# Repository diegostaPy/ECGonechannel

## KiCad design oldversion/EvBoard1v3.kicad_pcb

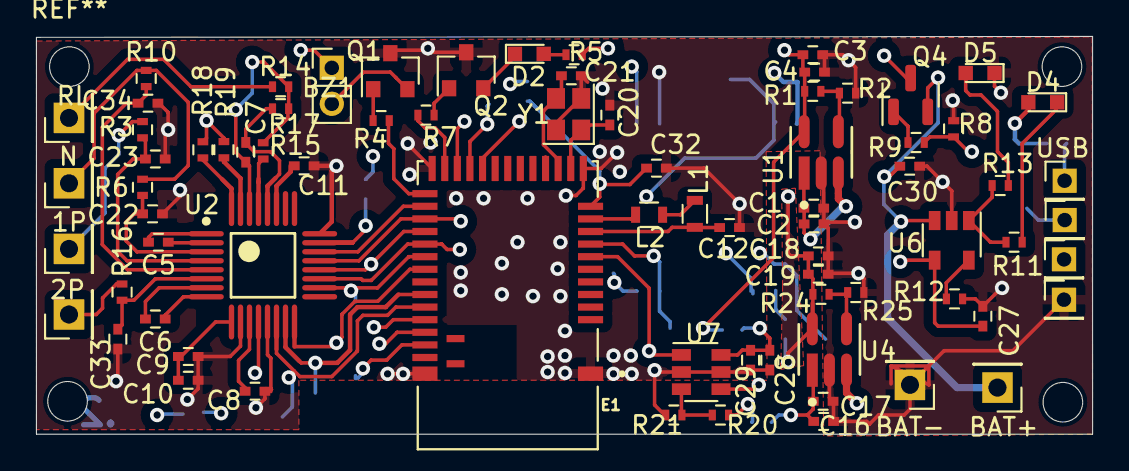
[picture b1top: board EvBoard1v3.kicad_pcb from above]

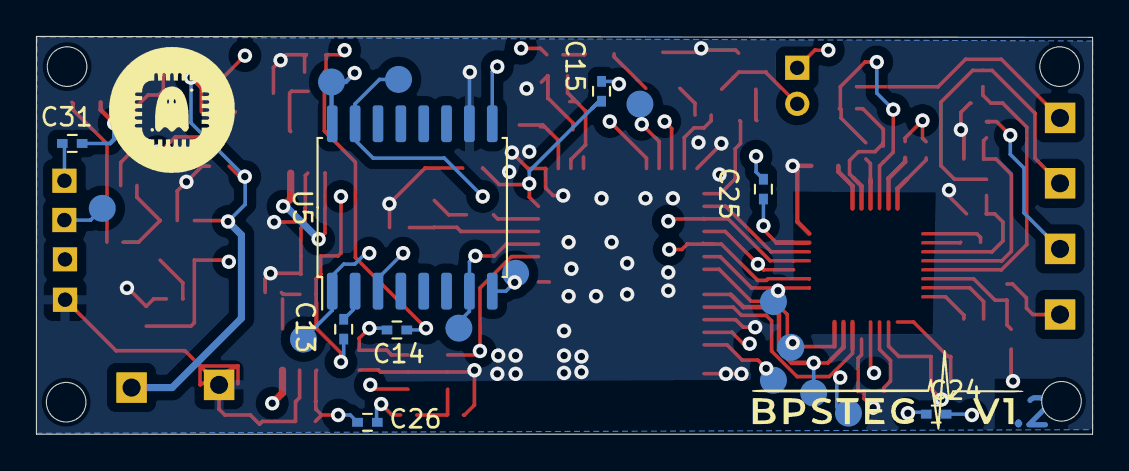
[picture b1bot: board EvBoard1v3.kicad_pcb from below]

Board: 4 copper layers, 58.7 x 22.1 mm, 91 parts (15 on the bottom side), 68 nets.

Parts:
1P, 2P: In_sensor1N; Pin_Header_Straight_1x01_Pitch2.54mm
BAT+: Conn_01x01; Pin_Header_Straight_1x01_Pitch2.54mm
BAT-: conn_gnd1; Pin_Header_Straight_1x01_Pitch2.54mm
BZ1: Buzzer; Pin_Header_Straight_1x02_Pitch2.00mm
C1, C3, C8, C11, C12, C16, C18, C27, C28, C30: 1uF; C_0402
C2, C4, C9, C17, C19, C29: 0.1uF; C_0402
C5, C6: 4.7nF; C_0402
C7: 1.5nF; C_0402
C10, C32: 10uF; C_0402
C13, C14, C15, C24, C25, C26, C31: 0; C_0402
C20, C21: 12pF; C_0402
C22, C23, C33, C34: 47pF; C_0402
D2, D4, D5: LED_Small; LED_0603
E1: MDBT42Q-512KV2; RAYTAC_MDBT42Q-512KV2
J6, J7, J8: Conn_01x01_Female; Pin_Header_Straight_1x01_Pitch2.00mm
L1: 10uH; L_0603
L2: 15nH; L_0603
N: In_sensor1; Pin_Header_Straight_1x01_Pitch2.54mm
Q1, Q2: Q_NPN_BCE; SOT-23
Q4: Q_PMOS_GSD; SOT-23
R1, R24: R1; R_0402
R2, R25: R2; R_0402
R3, R6, R10, R16, R18, R19: 30k; R_0402
R4, R7, R12: 2.2k; R_0402
R5, R11, R13: 470; R_0402
R8, R9, R20: 1k; R_0402
R14, R15: 100k; R_0402
R17: 1M; R_0402
R21: 10k; R_0402
RL: RLD_PIN; Pin_Header_Straight_1x01_Pitch2.54mm
TP3, TP4, TP5, TP6, TP8, TP8#2, TP12: TestPoint; Measurement_Point_Round-SMD-Pad_Small
U1, U4: ADP160AUJZ-3.0-R7; Analog_Devices-UJ-5-04_2017-B-IPC_A
U2: ADS1192IPBS; Texas_Instruments-ADS1192IPBS-Level_A
U5: W25Q128JVFIM; SOIC-16W_7.5x10.3mm_P1.27mm
U6: MCP73831-2-OT; SOT-23-5
U7: OPA847xDBV; SOT-23-6
USB: Conn_01x01_Female; Pin_Header_Straight_1x01_Pitch2.00mm
Y1: Crystal_GND24_Small; Crystal_SMD_2520-4pin_2.5x2.0mm

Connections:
BAT+: C1.1, C2.1, C16.1, C17.1, C26.2, Q4.3 (D), U1.1 (VIN), U1.3 (EN), U4.1 (VIN), U4.3 (EN)
BAT_AIN: E1.7 (P0.30), U7.1, U7.4 (-)
CLKsel: E1.34 (P0.20), TP3.1, U2.14 (CLKSEL)
CS_ADS: E1.30 (P0.16), TP4.1, U2.18 (~CS)
CS_FLASH: E1.8 (P0.31), U5.7 (CS)
DCLK: E1.36 (SWDCLK), J7.1
DIN: E1.29 (P0.15), TP5.1, U2.19 (DIN), U5.15 (DI(IO0))
DOUT: E1.27 (P0.13), U2.21 (DOUT), U5.8 (DO(IO1))
DREADY: E1.26 (P0.12), U2.22 (~DRDY)
Ddata: E1.37 (SWDIO), J6.1
GNDA: BAT-.1, C1.2, C2.2, C3.2, C4.2, C8.2, C9.2, C10.2, C11.2, C12.2, C16.2, C17.2, C18.2, C19.2, C20.1, C21.1, C22.2, C23.2, C27.1, C28.1, C29.1, C30.2, C32.2, C33.2, C34.2, D5.1 (K), E1.1 (GND), E1.12 (GND), E1.24 (GND), E1.35 (P0.21/RESET), E1.39 (GND), J8.1, Q1.3 (E), Q2.3 (E), R2.1, R8.2, R12.2, R21.2, R25.1, U1.2 (GND), U2.10 (VREFN), U2.13 (AVSS), U2.24 (DGND), U4.2 (GND), U5.10 (GND), U6.2 (VSS), U7.2 (V-), U7.5 (~DIS), Y1.2, Y1.4
HOLD_FLASH: E1.20 (P0.07), TP12.1, U5.1 (!HOLD_(IO3))
IN1N: C22.1, R6.2, U2.3 (IN1N)
IN1P: C23.1, R3.2, U2.4 (IN1P)
IN2N: C34.1, R10.2, U2.5 (IN2N)
IN2P: C33.1, R16.2, U2.6 (IN2P)
IN3N: R18.2, U2.32 (IN3N)
IN3P: R19.2, U2.31 (IN3P)
LED: E1.23 (P0.10), R7.2
unnamed: BZ1.2 (+), Q1.2 (C)
unnamed: C26.1, R20.1
unnamed: D2.2 (A), R5.2
unnamed: D2.1 (K), Q2.2 (C)
unnamed: D4.1 (K), R11.2
unnamed: D5.2 (A), R13.2
unnamed: E1.10 (DCC), L2.2
unnamed: C12.1, E1.9 (DEC4), L1.1
unnamed: C20.2, E1.13 (P0.00/XL1), Y1.1
unnamed: C21.2, E1.14 (P0.01/XL2), Y1.3
unnamed: C15.1, C32.1, E1.11 (VDD)
unnamed: C31.1, USB.1
unnamed: BAT+.1, C30.1, Q4.2 (S), U6.3 (VBAT)
unnamed: N.1, R6.1, R10.1
unnamed: 2P.1, R16.1
unnamed: R14.1, RL.1
unnamed: 1P.1, R3.1
unnamed: L1.2, L2.1
unnamed: Q1.1 (B), R4.1
unnamed: Q2.1 (B), R7.1
unnamed: Q4.1 (G), R9.2
unnamed: R1.1, R2.2, U1.4 (NC)
unnamed: C24.1, U2.12 (AVDD)
unnamed: C25.1, U2.23 (DVDD)
unnamed: C5.2, U2.1 (PGA1N)
unnamed: C5.1, U2.2 (PGA1P)
unnamed: C6.2, U2.7 (PGA2N)
unnamed: C6.1, U2.8 (PGA2P)
unnamed: C7.1, R17.1, U2.28 (RLDINV)
unnamed: R15.2, U2.29 (RLDIN/RLDREF)
unnamed: C7.2, R14.2, R15.1, R17.2, U2.30 (RLDOUT)
unnamed: C8.1, U2.11 (VCAP1)
unnamed: C11.1, U2.27 (VCAP2)
unnamed: C9.1, C10.1, U2.9 (VREFP)
unnamed: R24.1, R25.2, U4.4 (NC)
unnamed: C13.1, U5.2 (VCC)
unnamed: R12.1, U6.5 (PROG)
unnamed: R11.1, R13.1, U6.1 (STAT)
unnamed: R20.2, R21.1, U7.3 (+)
unnamed: C14.1, C28.2, C29.2, U7.6 (V+)
PWR: E1.33 (P0.19), TP8.1, U2.15 (~PWDN/~RESET)
RST_FLASH: E1.21 (P0.08), U5.3 (RST)
SCLK: E1.28 (P0.14), TP6.1, U2.20 (SCLK), U5.16 (CLK)
START: E1.31 (P0.17), TP8#2.1, U2.16 (START)
VBUS: C27.2, C31.2, D4.2 (A), R8.1, R9.1, U6.4 (VDD)
VDD: C13.2, C15.2, C18.1, C19.1, C25.2, R24.2, U4.5 (VOUT)
VDDA: BZ1.1 (-), C3.1, C4.1, C14.2, C24.2, R1.2, R5.1, R18.1, R19.1, U1.5 (VOUT)
WP_FLASH: E1.22 (P0.09), U5.9 (WP(IO2))
buzzer: E1.25 (P0.11), R4.2

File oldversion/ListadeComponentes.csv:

Reference(s),Value,LibPart,Footprint,Cambiar a un tamanho un poco mayor,,
C1,1uF,Device:C,Capacitors_SMD:C_0402,,,
C2,0.1uF,Device:C,Capacitors_SMD:C_0402,,,
C3,1uF,Device:C,Capacitors_SMD:C_0402,,,
C4,0.1uF,Device:C,Capacitors_SMD:C_0402,,,
C5,4.7nF,Device:C,Capacitors_SMD:C_0402,,,
C6,4.7nF,Device:C,Capacitors_SMD:C_0402,,,
C7,1.5nF,Device:C,Capacitors_SMD:C_0402,,,
C8,1uF,Device:C,Capacitors_SMD:C_0402,,,
C9,0.1uF,Device:C,Capacitors_SMD:C_0402,,,
C10,10uF,Device:C,Capacitors_SMD:C_0402,,,
C11,1uF,Device:C,Capacitors_SMD:C_0402,,,
C12,1uF,Device:C_Small,Capacitors_SMD:C_0402,,,
C13,0,Device:C_Small,Capacitors_SMD:C_0402,,,
C14,0,Device:C_Small,Capacitors_SMD:C_0402,,,
C15,0,Device:C_Small,Capacitors_SMD:C_0402,,,
C16,1uF,Device:C,Capacitors_SMD:C_0402,,,
C17,0.1uF,Device:C,Capacitors_SMD:C_0402,,,
C18,1uF,Device:C,Capacitors_SMD:C_0402,,,
C19,0.1uF,Device:C,Capacitors_SMD:C_0402,,,
C20,12pF,Device:C_Small,Capacitors_SMD:C_0402,,,
C21,12pF,Device:C_Small,Capacitors_SMD:C_0402,,,
C22,47pF,Device:C_Small,Capacitors_SMD:C_0402,,,
C23,47pF,Device:C_Small,Capacitors_SMD:C_0402,,,
C24,0,Device:C_Small,Capacitors_SMD:C_0402,,,
C25,0,Device:C_Small,Capacitors_SMD:C_0402,,,
C26,0,Device:C_Small,Capacitors_SMD:C_0402,,,
C27,1uF,Device:C_Small,Capacitors_SMD:C_0402,,,
C28,1uF,Device:C_Small,Capacitors_SMD:C_0402,,,
C29,0.1uF,Device:C_Small,Capacitors_SMD:C_0402,,,
C30,1uF,Device:C_Small,Capacitors_SMD:C_0402,,,
C31,0,Device:C_Small,Capacitors_SMD:C_0402,,,
C32,10uF,Device:C,Capacitors_SMD:C_0402,,,
C33,47pF,Device:C_Small,Capacitors_SMD:C_0402,,,
C34,47pF,Device:C_Small,Capacitors_SMD:C_0402,,,
D2,LED_Small,Device:LED_Small,LEDs:LED_0603,,,
D4,LED_Small,Device:LED_Small,LEDs:LED_0603,,,
D5,LED_Small,Device:LED_Small,LEDs:LED_0603,,,
E1,MDBT42Q-512KV2,MDBT42Q-512KV2:MDBT42Q-512KV2,RAYTAC_MDBT42Q-512KV2,,,
L1,10uH,Device:L_Small,Inductors_SMD:L_0603,,,
L2,15nH,Device:L_Small,Inductors_SMD:L_0603,,,
Q1,Q_NPN_BCE,Device:Q_NPN_BCE,TO_SOT_Packages_SMD:SOT-23,,,
Q2,Q_NPN_BCE,Device:Q_NPN_BCE,TO_SOT_Packages_SMD:SOT-23,,,
Q4,Q_PMOS_GSD,Device:Q_PMOS_GSD,Package_TO_SOT_SMD:SOT-23,,,
R1,R1,Device:R,Resistors_SMD:R_0402,,,
R2,R2,Device:R,Resistors_SMD:R_0402,,,
R3,30k,Device:R,Resistors_SMD:R_0402,,,
R4,2.2k,Device:R_Small,Resistors_SMD:R_0402,,,
R5,470,Device:R_Small,Resistors_SMD:R_0402,,,
R6,30k,Device:R,Resistors_SMD:R_0402,,,
R7,2.2k,Device:R_Small,Resistors_SMD:R_0402,,,
R8,1k,Device:R_Small,Resistors_SMD:R_0402,,,
R9,1k,Device:R_Small,Resistors_SMD:R_0402,,,
R10,30k,Device:R,Resistors_SMD:R_0402,,,
R11,470,Device:R_Small,Resistors_SMD:R_0402,,,
R12,2.2k,Device:R_Small,Resistors_SMD:R_0402,,,
R13,470,Device:R_Small,Resistors_SMD:R_0402,,,
R14,100k,Device:R,Resistors_SMD:R_0402,,,
R15,100k,Device:R,Resistors_SMD:R_0402,,,
R16,30k,Device:R,Resistors_SMD:R_0402,,,
R17,1M,Device:R,Resistors_SMD:R_0402,,,
R18,30k,Device:R,Resistors_SMD:R_0402,,,
R19,30k,Device:R,Resistors_SMD:R_0402,,,
R20,1k,Device:R_Small,Resistors_SMD:R_0402,,,
R21,10k,Device:R_Small,Resistors_SMD:R_0402,,,
R24,R1,Device:R,Resistors_SMD:R_0402,,,
R25,R2,Device:R,Resistors_SMD:R_0402,,,
U1,ADP160AUJZ-3.0-R7,EvBoard1-rescue:ADP160AUJZ-3.0-R7-eecADP,adp:Analog_Devices-UJ-5-04_2017-B-IPC_A,,,
U2,Cambiar,EvBoard1-rescue:ADS1192IPBS-eec,eec:Texas_Instruments-ADS1192IPBS-Level_A,,,
U4,ADP160AUJZ-3.0-R7,EvBoard1-rescue:ADP160AUJZ-3.0-R7-eecADP,adp:Analog_Devices-UJ-5-04_2017-B-IPC_A,,,
U5,Cambiar,,,,,
U6,MCP73831-2-OT,Battery_Management:MCP73831-2-OT,TO_SOT_Packages_SMD:SOT-23-5,,,
U7,OPA847xDBV,Amplifier_Operational:OPA847xDBV,TO_SOT_Packages_SMD:SOT-23-6,,,
Y1,Cambiar,,,,,cambiar

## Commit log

2023-08-16 comite inicial
2023-08-16 actualizacion
